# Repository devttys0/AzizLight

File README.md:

Introduction
============

This circuit allows the user to turn an AC outlet on or off using a simple (or not so simple!) phrase, such as "Aziz, light!!". Note that it is not an intelligent circuit in that it does not repsond to specific commands, but only to the amplitude of the detected speech.

It does, however, provide the *illusion* of intelligence, as well as mitigations against false positive responses that typically plague such simple voice-activated circuits.

Functional Overview
===================

The circuit is activated by any sound that is loud enough, and persists long enough, to trigger it. The trigger sensitivity is user-adjustable, and can be configured to either turn an AC outlet on or off when triggered.

Once the circuit is triggered, it will wait until the sound stops before activating the trigger output; this allows users to turn the outlet on/off using any arbitrarily long phrase ("Aziz, light!", "Turn out those lights!", "It's dark in here, I can't see a thing!", etc).

In the absense of any subsequent sound(s), the trigger output will remain on for approximately 60 seconds before turning off again. During this period, the trigger output cannot be turned off by any additional sound or noise.

False positive triggers are unavoidable in any voice-activated system. This circuit attempts to prevent/mitigate false positive responses by:

 1. Ignoring low-level audio signals.
 2. Filtering out very high or low frequency audio signals.
 3. The cricuit can either turn the AC outlet on or off, **not both** (the desired action can be selected via a toggle switch).
 4. The circuit will only activate for a short period of time (~60 seconds).

Mitigation #1 prevents softer sounds from building up a voltage sufficient to trigger the circuit.

Mitigation #2 provides immunity from triggering on obviously unwanted audio.

Mitigation #3 is included to prevent systems connected to the AC outlet from accidentally turning themselves off. Otherwise, if using this circuit to turn on, say, a TV, the audio output of the TV may re-activate the circuit and turn the TV back off (a common problem with "the clapper").

Mitigation #4 ensures that the effect of any false positive trigger(s) is only temporary; it also serves to more accurately simulate a sleepy "Aziz", which was the original inspiration for this circuit.

Circuit Description
===================

The circuit is comprised of two comparators and three op amps, which provide the necessary blocks for operation:

 1. Audio amplifier
 2. Level detection
 3. Signal processing / logic control
 4. Relay driver

Audio Amplifier
---------------

Op amp U1A serves to amplify the audio signal from the electret microphone (MIC1). Resistors R11 and R16 set the gain at 100.

R11 also provides biasing to the electret microphone, with R11 and C5 forming a high-pass filter with a cutoff at 284Hz. R16 and C8 form a low-pass filter with a cutoff frequency at 2.8kHz. This provides a ~2.5kHz passband, attenuating higher or lower frequency sounds.

Signal Processing
-----------------

Comparator U2A monitors the amplified signal's voltage, only outputting a logic '1' (+5V) if the peak voltage exceeds the set threshold voltage. The threshold voltage is set by R19, R21, R23, and potentiometer RV1, where RV1 provides an adjustable sensitivity setting by changing the minimum threshold voltage. Note that the hysteresis resistors R2 and R13 also affect the threshold voltage, but are fixed and not adjustable.

The purpose for setting this minimum threshold voltage is to ensure that a sequence of low-amplitude audio signals do not build up charge on capacitor C6 and ultimately trigger relay K1; the user-adjustable sensitivity control is an added bonus.

Comparator U2A's output is used to charge capacitor C6 via resistor R1 (U2 has an open-collector output) and diode D1. This allows charge to build up on C6 over time; this charge is bled off slowly via resistors R15 and R18, while op amp U1B provides a high-impedance isolation buffer between C6 and the rest of the circuit.

The delay caused by the charging of C6 is desirable, as it prevents short sounds from raising the voltage on C6 beyond the trigger voltage threshold. This prevents false positive triggers from short-lived noises.

The slow bleed off of C6 is necessary so that a) audio signals do not cause a build up of charge over an indefinite period of time, and b) once activated, the relay is turned off after some period of time.

Level Detection
---------------

Comparator U2B monitors the voltage of C6 and outputs a logic "1" (+5V) when C6's voltage reaches the comparator's logic-high threshold voltage which is set by R20 and R22, as well as the hysteresis resistors R10 and R14. Once this threshold voltage is reached, U2B's output will go high and the circuit is triggered.

Being an open-collector output, the +5V from the comparator charges capacitor C7 via resistor R6. This delays the turn on of transistor Q2. When C7's voltage is large enough, it will turn on Q2 which, in turn, will turn off Q1 and Q3.

To maintain the illusion of intelligence, C7's voltage must be kept below Q2's Vgs until after the user is finished speaking their phrase. To ensure this, C8 is discharged through transistor Q4 whenever the input audio amplitude is loud enough to trigger comparator U2A. This way, as long as the user continues talking, C7 will be continually discharged, and Q2 will remain off. After a short pause however, C7 will charge up and turn on Q2.

Once activated, the output must remain latched for the time constant determined by C6 and R15+R18 (see "Signal Processing" above). Transistor Q3 is included to ensure that any audio input does not prematurely turn off Q2 by discharging C7 through Q4. When Q2 is turn on, Q3 will be turned off, preventing C7 from discharging through Q4, regardless of any input audio.

Transistors Q1 and Q2 provide inverted and non-inverted logic outputs, respectively, which can be selected from by switch SW2. If the output is taken from Q2, then the relay will be normally off, and will be turned on when a verbal command is given; if the output is taken from Q1, then the relay will be normally on, and will be turned off when a verbal command is given. Note that these settings are mutually exclusive.

When the voltage on C6 bleeds off below U2B's logic-low threshold level, U2B will turn off. This means that the voice-activated command will only take effect for a finite period of time (about 60 seconds, depending on the charge of C6).

Resistor R17 is included to de-Q any potential LC resonant circuit formed between Q1/Q3's gate capacitances and inductance of the wires connecting them to switch SW2.

Relay Driver
------------

Transistor Q5 serves to isolate the logic circuitry from the relay driver circuitry. This is necessary in the likely event that the relay drier circtuiry is comprised of an optoisolator or BJT transistor. Without Q5, the voltage drop incurred by the PN junction could affect the logic circuitry's voltage levels.

The relay driver circuitry is housed in a separate enclosure from the rest of the circuit, and is used to drive relay K1 on/off in order to turn a standard AC outlet on/off. A standard audio cable was used to connect the control circuitry to the relay driver board.

Transistor Q6 drives the relay's inductor. Diode D7 is a flyback diode, which protects Q6 from the inductive kick-back of suddenly removing current from K1's inductor.

Switch SW3 provides a manual override to always turn the AC outlet on, if desired.

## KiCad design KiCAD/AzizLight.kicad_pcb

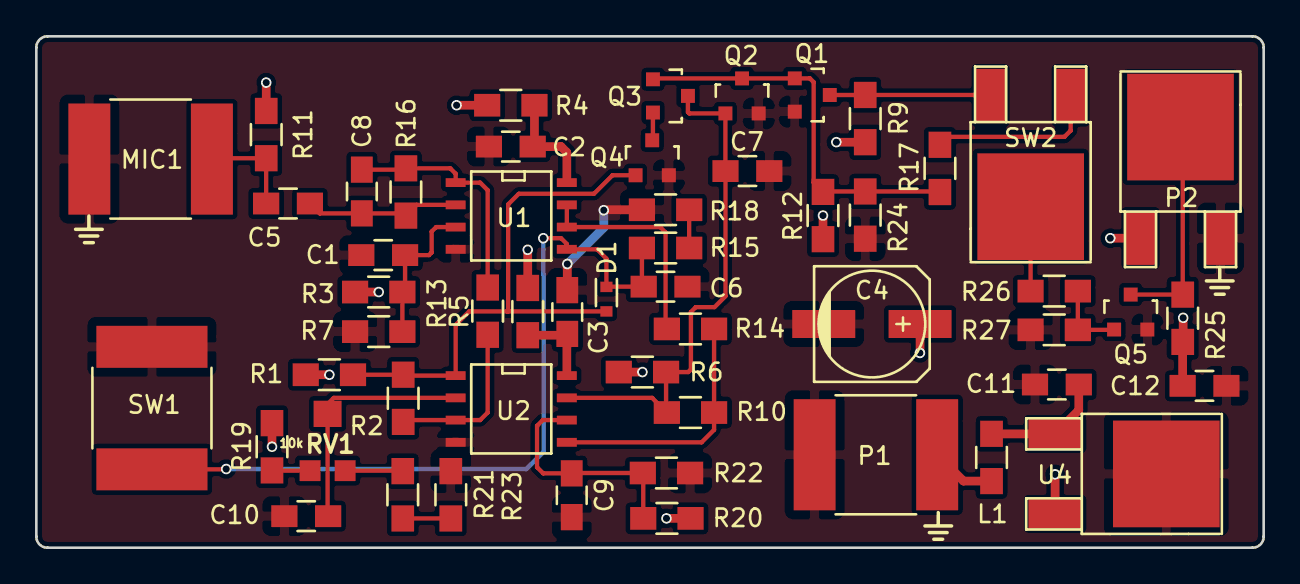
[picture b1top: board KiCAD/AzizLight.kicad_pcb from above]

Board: 2 copper layers, 70.1 x 29.2 mm, 54 parts (0 on the bottom side), 29 nets.

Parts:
C1, C2, C3, C5, C9, C10, C12: 0.1uF; C_0805_HandSoldering
C4: 100uF; c_elec_6.3x5.8
C6, C7: 10uF; C_0805_HandSoldering
C8: 100pF; C_0805_HandSoldering
C11: 0.33uF; C_0805_HandSoldering
D1: 1N4148; SOD-523
L1: 10uH; R_0805_HandSoldering
MIC1: POM-3535; C_2225_HandSoldering
P1: +9V; C_2225_HandSoldering
P2: Trigger Out; TO-252-2Lead
Q1, Q2, Q3, Q4, Q5: BS170; SOT-23
R1, R3, R7, R13, R19, R21, R22, R23: 10k; R_0805_HandSoldering
R2: 220k; R_0805_HandSoldering
R4, R5, R17, R26: 100; R_0805_HandSoldering
R6: 100k; R_0805_HandSoldering
R9, R12, R25: 4.7k; R_0805_HandSoldering
R10: 470k; R_0805_HandSoldering
R11: 5.6k; R_0805_HandSoldering
R14: 120k; R_0805_HandSoldering
R15, R18: 10M; R_0805_HandSoldering
R16: 560k; R_0805_HandSoldering
R20: 12k; R_0805_HandSoldering
R24, R27: 1M; R_0805_HandSoldering
RV1: 10k; TRIMPOT_SMD
SW1: Reset; C_2225_HandSoldering
SW2: Invert; TO-252-2Lead
U1: MCP602; SOIC-8-N
U2: LM393; SOIC-8-N
U4: MC7805; TO-252-2Lead

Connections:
+5V: C4.1, C12.1, P2.1, R1.2, R3.1, R4.1, R5.1, R6.1, R9.1, R11.1, R12.1, R19.2, R20.1, R25.1, U4.3
GND: C1.2, C2.1, C3.1, C4.2, C6.2, C7.2, C9.2, C10.2, C11.2, C12.2, MIC1.2, P1.1, P2.3, Q1.2, Q2.2, Q4.2, Q5.2, R7.2, R18.1, R22.1, R23.1, R24.1, R27.1, SW1.1, U1.4, U2.4, U4.2
unnamed: C1.1, R3.2, R7.1, U1.3
unnamed: C2.2, R4.2, U1.8
unnamed: C3.2, R5.2, U2.8
unnamed: C5.1, C8.2, R16.2, U1.2
unnamed: C5.2, MIC1.1, R11.2
unnamed: C6.1, D1.1, R15.2, SW1.2, U1.5
unnamed: C7.1, Q2.1, Q3.3, R6.2, R10.1, U2.7
unnamed: C8.1, R13.2, R16.1, U1.1
unnamed: C9.1, R20.2, R22.2, U2.6
unnamed: C10.1, RV1.2, U2.2
unnamed: C11.1, L1.2, U4.1
unnamed: D1.2, Q4.1, R1.1, R2.1, U2.1
unnamed: L1.1, P1.2
unnamed: P2.2, Q5.3, R25.2
unnamed: Q1.1, Q2.3, Q3.1, R12.2, R17.2, R24.2
unnamed: Q1.3, R9.2, SW2.3
unnamed: Q3.2, Q4.3
unnamed: Q5.1, R26.1, R27.2
unnamed: R10.2, R14.1, U2.5
unnamed: R2.2, R13.1, U2.3
unnamed: R14.2, U1.6, U1.7
unnamed: R15.1, R18.2
unnamed: R17.1, SW2.1
unnamed: R19.1, RV1.1
unnamed: R21.1, R23.2
unnamed: R21.2, RV1.3
unnamed: R26.2, SW2.2

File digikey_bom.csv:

1,1N4148XTPMSCT-ND,D1
1,587-2045-1-ND,L1
3,311-4.70KCRCT-ND,R12|R25|R9
1,311-12.0KCRCT-ND,R20
1,668-1391-ND,MIC1
2,311-10.0MCRCT-ND,R15|R18
1,311-470KCRCT-ND,R10
1,311-220KCRCT-ND,R2
1,MCP602T-I/SNCT-ND,U1
1,311-100KCRCT-ND,R6
7,490-4789-1-ND,C1|C10|C12|C2|C3|C5|C9
4,311-100CRCT-ND,R17|R26|R4|R5
1,490-6462-1-ND,C11
8,311-10.0KCRCT-ND,R1|R13|R19|R21|R22|R23|R3|R7
1,PCE3898CT-ND,C4
2,490-6477-1-ND,C6|C7
1,MC7805BDTRKGOSCT-ND,U4
1,TC33X-103ECT-ND,RV1
1,311-5.60KCRCT-ND,R11
1,311-560KCRCT-ND,R16
2,311-1.00MCRCT-ND,R24|R27
1,399-1122-1-ND,C8
1,311-120KCRCT-ND,R14
1,497-1593-1-ND,U2
5,BS170FCT-ND,Q1|Q2|Q3|Q4|Q5

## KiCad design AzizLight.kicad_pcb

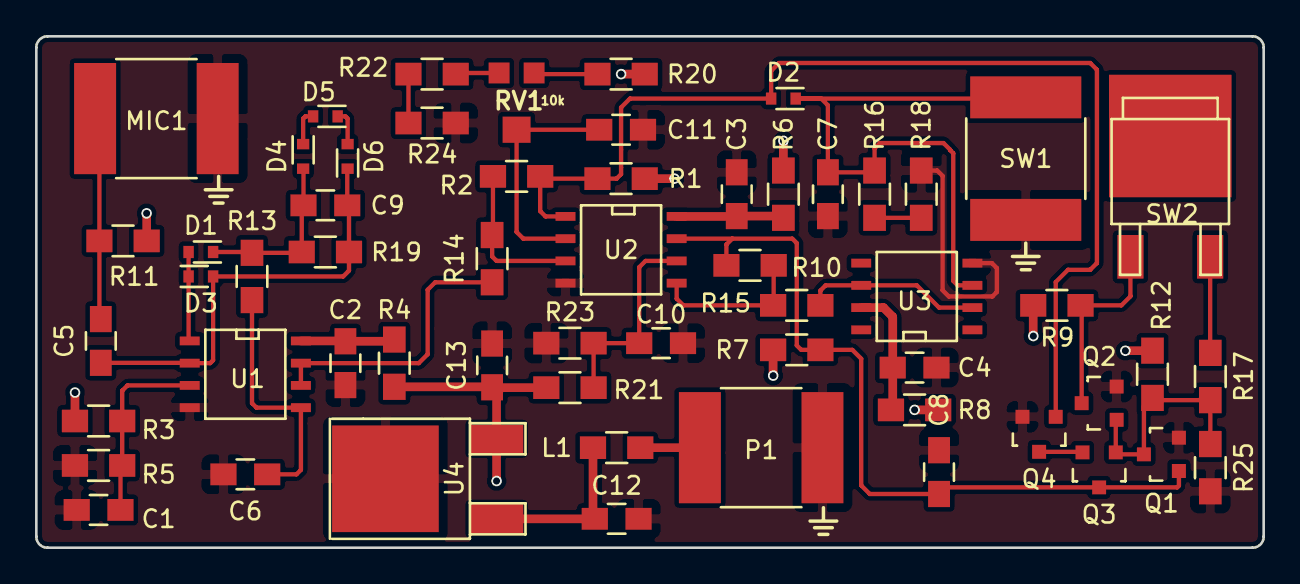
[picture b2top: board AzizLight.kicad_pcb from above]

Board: 2 copper layers, 70.1 x 29.2 mm, 58 parts (0 on the bottom side), 32 nets.

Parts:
C1, C2, C3, C4, C5, C6, C10, C11, C13: 0.1uF; C_0805_HandSoldering
C7, C8: 10uF; C_0805_HandSoldering
C9: 100pF; C_0805_HandSoldering
C12: 0.33uF; C_0805_HandSoldering
D1, D2, D3, D4, D5, D6: 1N4148; SOD-523
L1: 10uH; R_0805_HandSoldering
MIC1: POM-3535; C_2225_HandSoldering
P1: +9V; C_2225_HandSoldering
Q1, Q2, Q3, Q4: BS170; SOT-23
R1: 68k; R_0805_HandSoldering
R2: 220k; R_0805_HandSoldering
R3, R5, R13, R14, R20, R22, R23, R24: 10k; R_0805_HandSoldering
R4, R6, R8: 100; R_0805_HandSoldering
R7: 100k; R_0805_HandSoldering
R9, R12, R17: 4.7k; R_0805_HandSoldering
R10: 470k; R_0805_HandSoldering
R11: 5.6k; R_0805_HandSoldering
R15: 120k; R_0805_HandSoldering
R16, R18: 10M; R_0805_HandSoldering
R19: 560k; R_0805_HandSoldering
R21: 12k; R_0805_HandSoldering
R25: 1M; R_0805_HandSoldering
RV1: 10k; TRIMPOT_SMD
SW1: Reset; C_2225_HandSoldering
SW2: Invert; SOT-428
U1: MCP602; SOIC-8-N
U2: LM393; SOIC-8-N
U3: MCP601; SOIC-8-N
U4: MC7805; TO-252-2Lead

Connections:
+5V: C13.1, R1.2, R3.1, R4.1, R6.1, R7.1, R8.1, R9.1, R11.1, R12.1, R20.2, R21.1, U4.3
GND: C1.2, C2.1, C3.1, C4.1, C6.2, C7.2, C8.2, C10.2, C11.2, C12.2, C13.2, MIC1.2, P1.1, Q1.2, Q2.2, Q4.2, R5.2, R18.1, R23.1, R24.1, R25.1, SW1.1, U1.4, U2.4, U3.4, U4.2
unnamed: C1.1, R3.2, R5.1, U1.3
unnamed: C2.2, R4.2, U1.8
unnamed: C3.2, R6.2, U2.8
unnamed: C4.2, R8.2, U3.7
unnamed: C5.1, C9.2, D3.2, D6.1, R19.2, U1.2
unnamed: C5.2, MIC1.1, R11.2
unnamed: C6.1, R13.1, U1.5
unnamed: C7.1, D2.1, R16.2, SW1.2, U3.3
unnamed: C8.1, Q1.1, Q3.3, R7.2, R10.1, U2.7
unnamed: C9.1, D1.1, D4.2, R13.2, R19.1
unnamed: C10.1, R21.2, R23.2, U2.6
unnamed: C11.1, RV1.2, U2.2
unnamed: C12.1, L1.2, U4.1
unnamed: D1.2, D3.1, U1.1
unnamed: D2.2, Q4.1, R1.1, R2.1, U2.1
unnamed: D4.1, D5.2
unnamed: D5.1, D6.2
unnamed: L1.1, P1.2
unnamed: Q1.3, Q2.1, Q3.1, R12.2, R17.2, R25.2
unnamed: Q2.3, R9.2, SW2.1
unnamed: Q3.2, Q4.3
unnamed: R10.2, R15.1, U2.5
unnamed: R2.2, R14.1, U2.3
unnamed: R14.2, U1.6, U1.7
unnamed: R15.2, U3.2, U3.6
unnamed: R16.1, R18.2
unnamed: R17.1, SW2.3
unnamed: R20.1, RV1.1
unnamed: R22.1, R24.2
unnamed: R22.2, RV1.3

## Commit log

2016-10-13 Fixed wiring of diode D3, updated README
2016-10-13 Updated schematic page properties
2016-10-13 Updated README, added L1, C12, C13 values.
2016-10-14 Added logic to prevent activation until after the key phrase is finished
2016-10-14 Minor README update
2016-10-15 Minor schematic changes, all footprints assigned, netlist generated
2016-10-15 Moved relay driver circuitry to separate file
2016-10-15 Fixed footprint issues
2016-10-15 Initial PCB design
2016-10-15 Added fp-lib-table
2016-10-15 PCB layout finished.
2016-10-15 Updated relay driver annotations
2016-10-15 Minor PCB update
2016-10-16 Updated PCB for more efficient layout
2016-10-16 Added gerber files
2016-10-16 Modified SW2 solder pads.
2016-10-16 Fixed readme component references
2016-10-16 Directory re-structure
2016-10-17 Moved libs into KiCAD
2016-10-18 v1.3 commit
2016-10-19 Added BOM and PDF schematic
2016-10-19 Added pull down resistor R28
2016-10-19 Updated schematic and BOM files
